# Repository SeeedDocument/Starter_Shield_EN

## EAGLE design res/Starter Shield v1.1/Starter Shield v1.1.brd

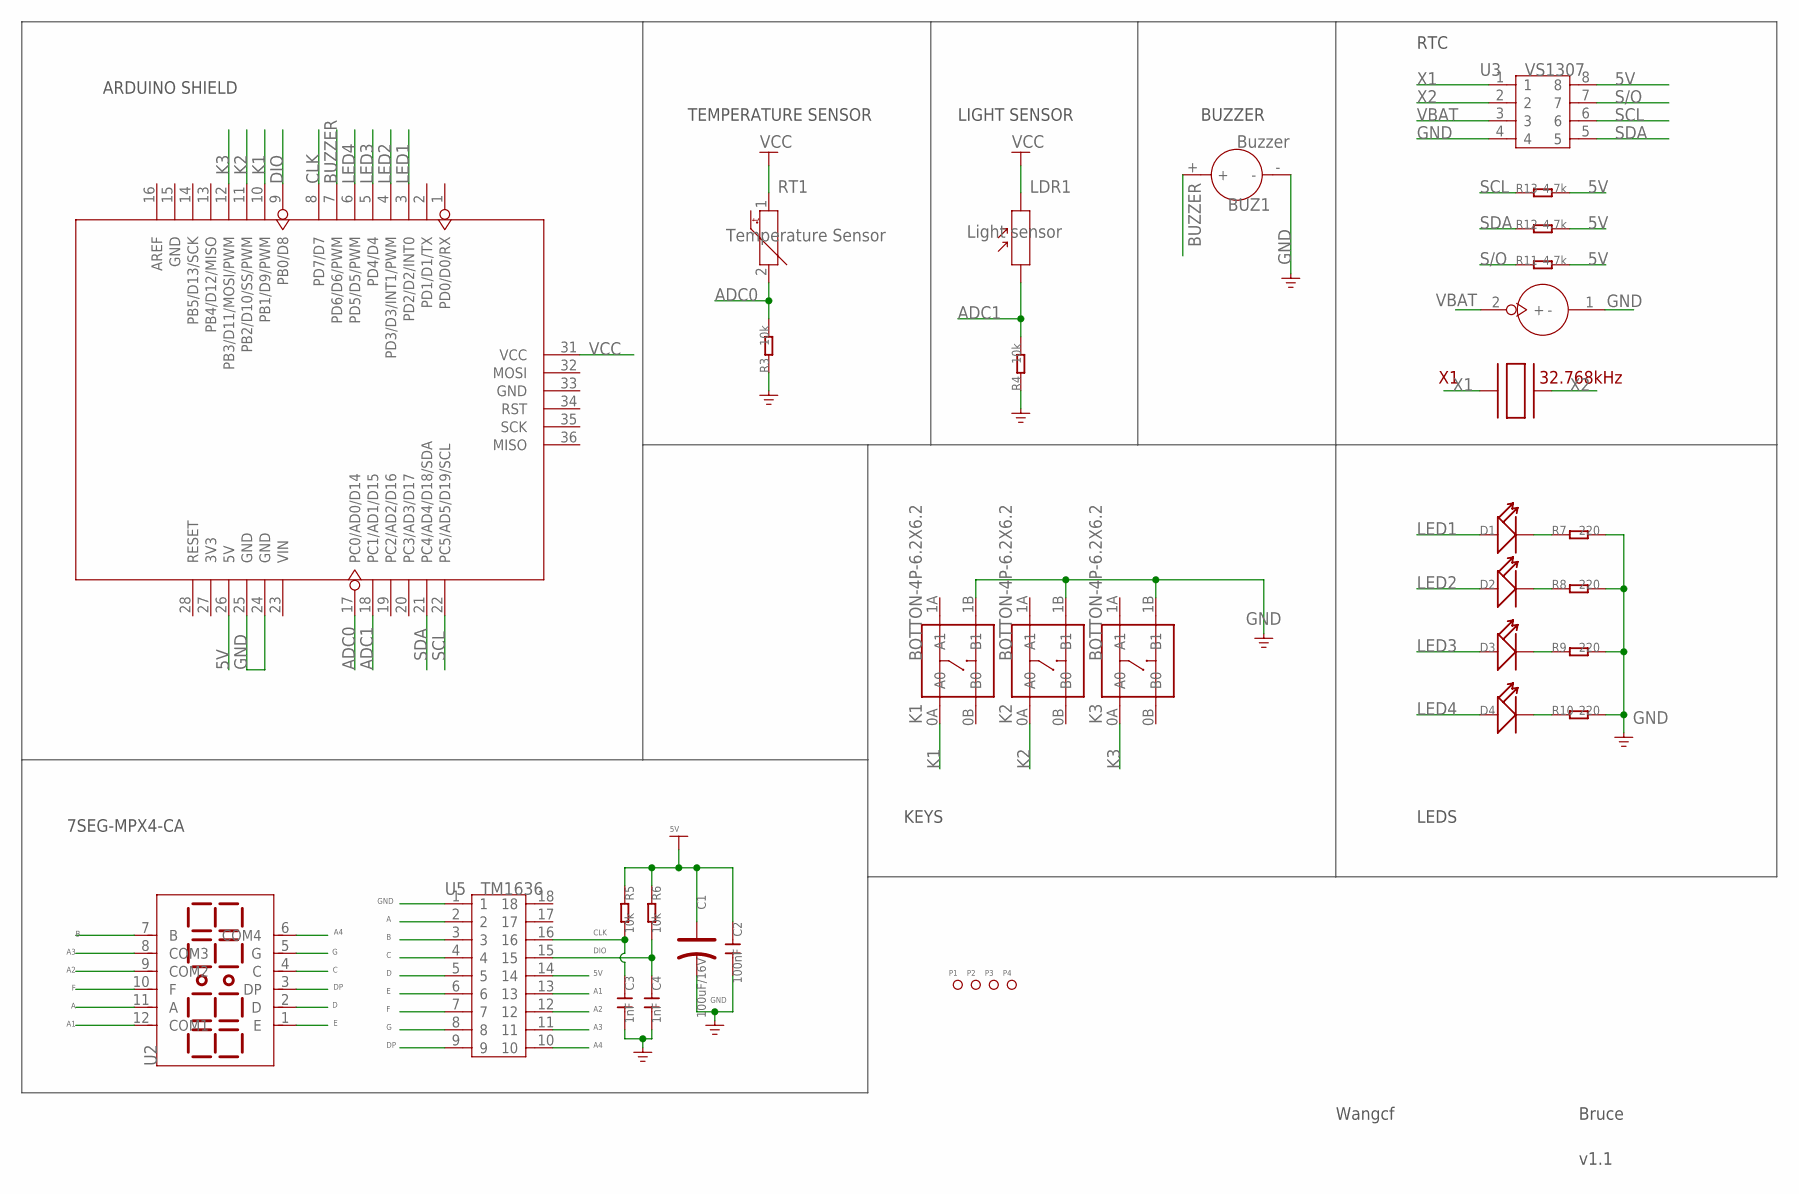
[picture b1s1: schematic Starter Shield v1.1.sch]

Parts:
BATT1: BATTERYBATTERY1225_SMT; BATTERY1225_SMT
BUZ1: Buzzer; 2P-7.6-D12X6.5H
C1: 100uF/16V; ELECTRO-5.3MM
C2: 100nF; CERAMIC-2.54
C3, C4: 1nF; CERAMIC-2.54
D1, D2, D3, D4: LED-3MM; LED-2P-2.54-3MM
K1, K2, K3: BOTTON-4P-6.2X6.2; 4P-8X8
LDR1: Light sensor; 5528
P1, P2, P3, P4: PAD-MARK; ROUND-MARK-1.0
R3, R4, R5, R6: 10k; R0207/7
R7, R8, R9, R10: 220; R0207/7
R11, R12, R13: 4.7k; R0207/7
RT1: Temperature Sensor; 2P-2.54-D3.0MM
U1: ARDUINO'W/-SILK; ARDUINO
U2: LED-4-BIT-7-SEG'SR430563K'; 7-4-BIT-SEG-2.54-50X19X8H
U3: VS1307; DIP8
U5: TM1636; DIP18
X1: 32.768kHz; XTL_S

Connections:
5V: C1.+, C2.1, R5.1, R6.1, R11.2, R12.2, R13.2, U1.26 (5V), U3.8, U5.14
A: U2.11 (A), U5.2
A1: U2.12 (COM1), U5.13
A2: U2.9 (COM2), U5.12
A3: U2.8 (COM3), U5.11
A4: U2.6 (COM4), U5.10
ADC0: R3.2, RT1.2, U1.17 (PC0/AD0/D14)
ADC1: LDR1.1, R4.2, U1.18 (PC1/AD1/D15)
B: U2.7 (B), U5.3
BUZZER: BUZ1.+, U1.7 (PD6/D6/PWM)
C: U2.4 (C), U5.4
CLK: C3.1, R5.2, U1.8 (PD7/D7), U5.16
D: U2.2 (D), U5.5
DIO: C4.1, R6.2, U1.9 (PB0/D8), U5.15
DP: U2.3 (DP), U5.9
E: U2.1 (E), U5.6
F: U2.10 (F), U5.7
G: U2.5 (G), U5.8
GND: BATT1.1 (-), BUZ1.-, C1.-, C2.2, C3.2, C4.2, K1.1B (B1), K2.1B (B1), K3.1B (B1), R3.1, R4.1, R7.2, R8.2, R9.2, R10.2, U1.24 (GND), U1.25 (GND), U3.4, U5.1
K1: K1.0A (A0), U1.10 (PB1/D9/PWM)
K2: K2.0A (A0), U1.11 (PB2/D10/SS/PWM)
K3: K3.0A (A0), U1.12 (PB3/D11/MOSI/PWM)
LED1: D1.A (+), U1.3 (PD2/D2/INT0)
LED2: D2.A (+), U1.4 (PD3/D3/INT1/PWM)
LED3: D3.A (+), U1.5 (PD4/D4)
LED4: D4.A (+), U1.6 (PD5/D5/PWM)
unnamed: D1.K (-), R7.1
unnamed: D2.K (-), R8.1
unnamed: D3.K (-), R9.1
unnamed: D4.K (-), R10.1
S/O: R11.1, U3.7
SCL: R13.1, U1.22 (PC5/AD5/D19/SCL), U3.6
SDA: R12.1, U1.21 (PC4/AD4/D18/SDA), U3.5
VBAT: BATT1.2 (+), U3.3
VCC: LDR1.2, RT1.1, U1.31 (VCC)
X1: U3.1, X1.1
X2: U3.2, X1.2

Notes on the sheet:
TEMPERATURE SENSOR
LIGHT SENSOR
7SEG-MPX4-CA
BUZZER
KEYS
LEDS
ARDUINO SHIELD
RTC
Wangcf
v1.1
Bruce

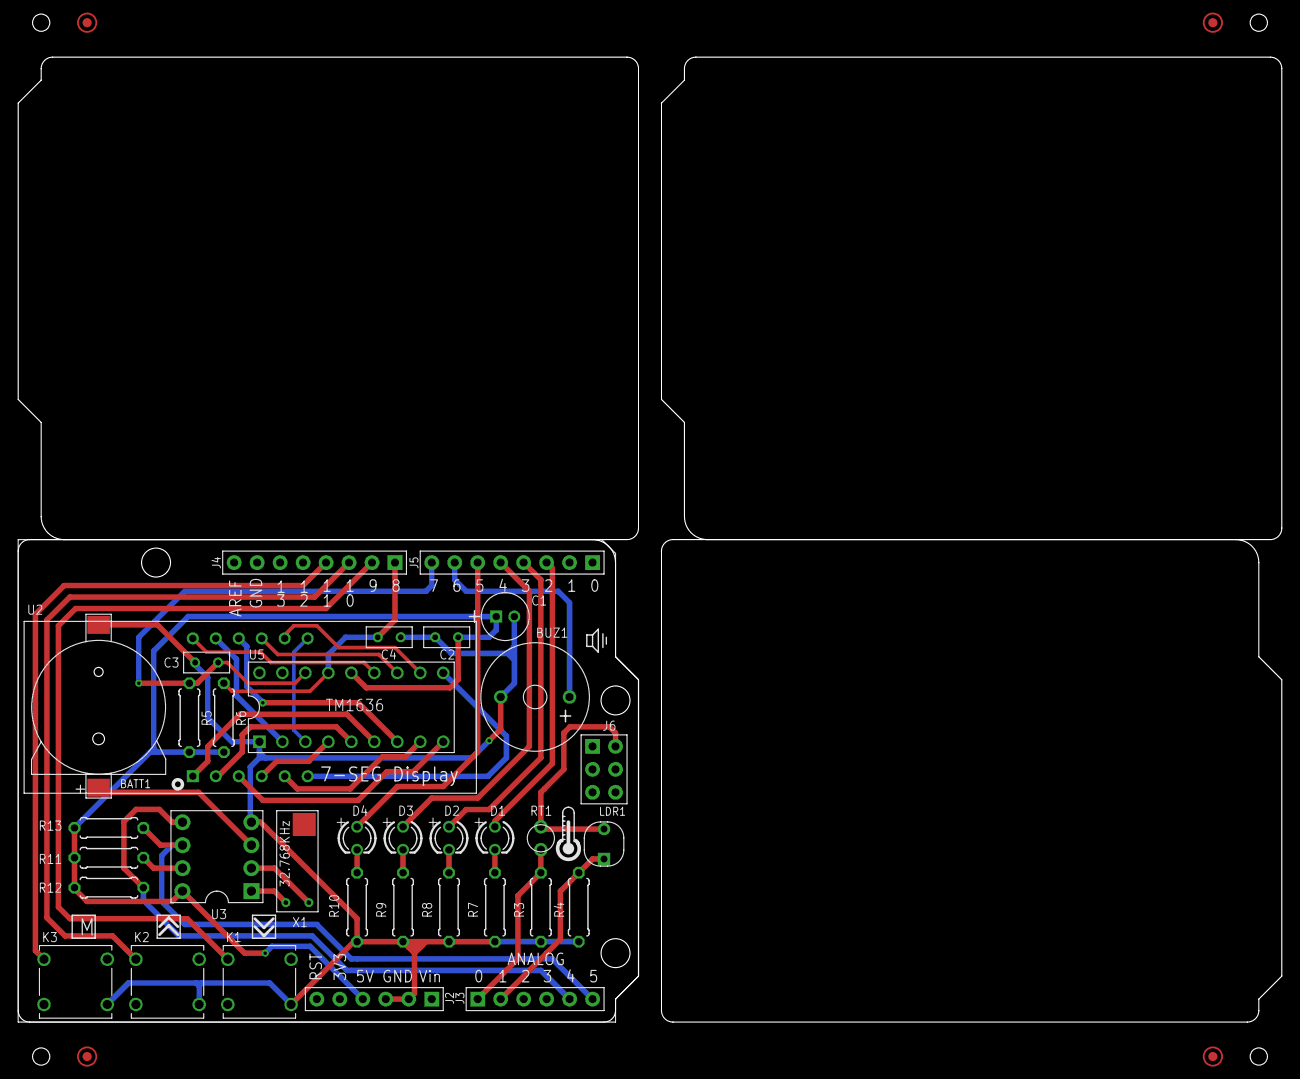
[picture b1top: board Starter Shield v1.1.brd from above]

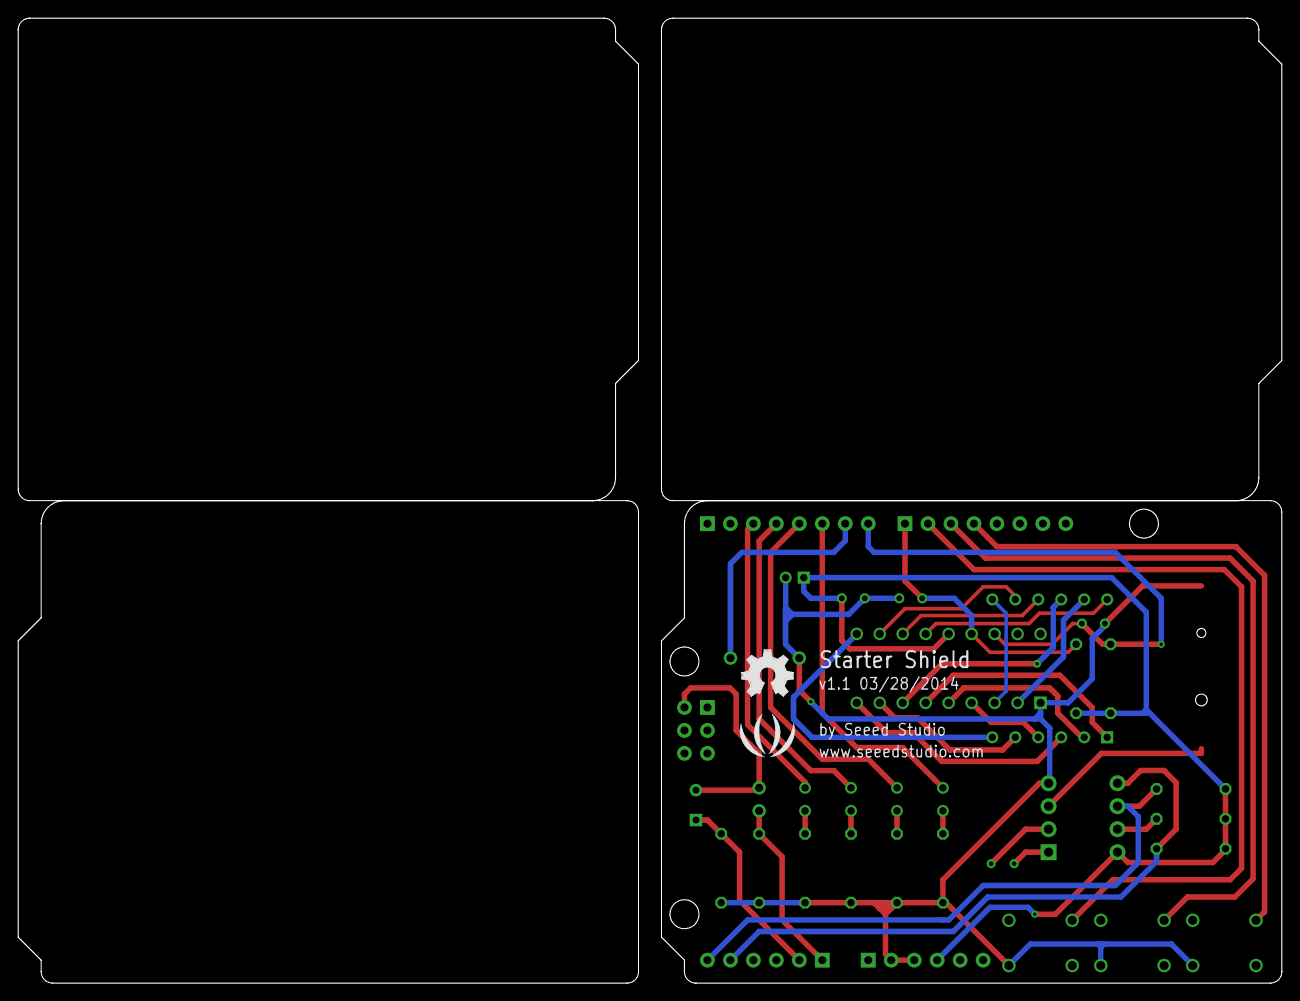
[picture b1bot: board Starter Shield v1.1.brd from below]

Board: 2 copper layers, 139.7 x 106.7 mm, 37 parts (2 on the bottom side), 37 nets.

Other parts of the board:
U$11: LOGO_SILK
U$12: OSHW_FILLX200_NOTEXT

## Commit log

2017-06-09 upgrade
